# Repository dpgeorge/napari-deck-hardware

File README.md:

Napari Deck Hardware
====================

The Napari Deck is a custom keyboard-like USB HID input device with keys,
sliders, encoders and trackpads.  It is optimised for controlling [napari],
a multi-dimensional image viewer.

This repository contains the hardware design files needed to build a Napari
Deck: parts lists, 3D printed housing files and PCB design files.

Deck v1
-------

Napari Deck v1 is the first iteration of the housing and inputs (encoders, sliders,
buttons).  It is used to evaluate the inputs and the general layout of the deck.

It has the following inputs:
- mini trackball at the thumb position
- two keyboard switches
- two encoders
- iPod-like dial with encoder and five buttons
- mini joystick
- a slider (linear potentiometer)

Deck v2
-------

Napari Deck v2 is the second iteration of the housing and inputs, and is a fully
functional USB HID device that works with napari using `napari-deck-plugin`.

It has the following inputs:
- mini joystick at the thumb position for 3D rotation
- mini trackball at the thumb position for panning
- two encoders at the thumb position for rotation and zoom
- 16 keyboard switches
- three encoders for 3-axis slicing
- two sliders for opacity and brush size
- two sliders combined with a selection switch for four clipping planes

Deck mini
---------

Napari Deck Mini is a small device used to evaluate a mini trackpad and an encoder.
It is fully functional and works with napari.

It has the following inputs:
- mini trackpad
- encoder

Deck v3
-------

Napari Deck v3 is the third iteration of the housing and inputs.  It has a custom
PCB to simplify the construction, with a built-in STM32G0B1 microcontroller.

It has the following inputs:
- two mini trackpads at the thumb position for 2D panning and 3D rotation
- two encoders at the thumb position for zoom and 3D rotation
- 16 keyboard switches
- three encoders for 3-axis slicing
- two sliders for opacity and brush size
- two sliders combined with a 4-way selection switch for eight clipping planes

Deck v3 is currently a work-in-progress.

[napari]: https://github.com/napari/napari

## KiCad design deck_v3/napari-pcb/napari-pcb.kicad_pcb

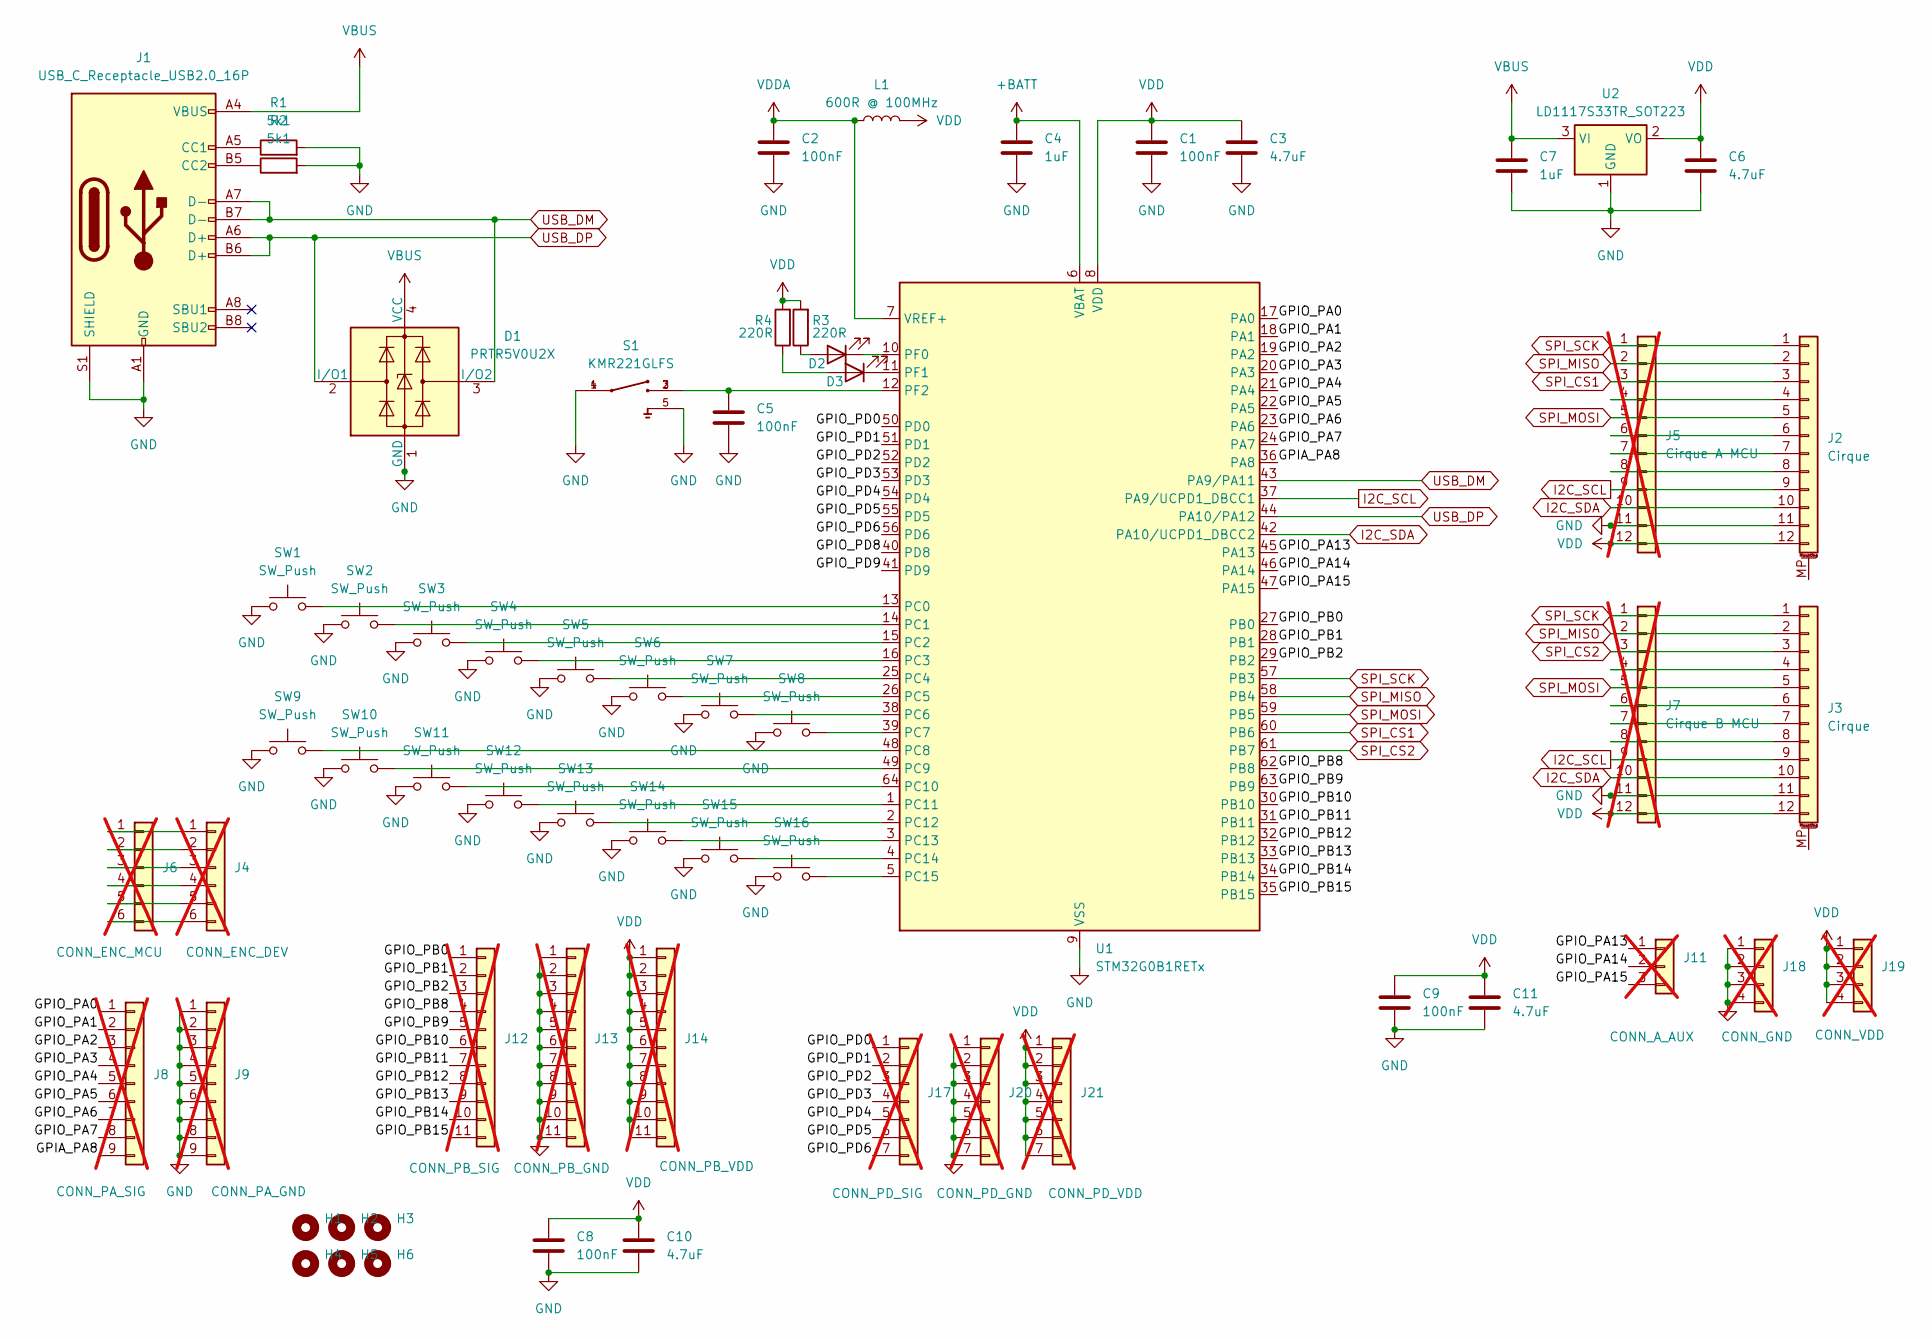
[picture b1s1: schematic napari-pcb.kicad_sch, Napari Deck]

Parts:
C1, C2, C5, C8, C9: 100nF; C_0603_1608Metric; LCSC Part # C14663
C3, C6, C10, C11: 4.7uF; C_0805_2012Metric; LCSC Part # C1779
C4, C7: 1uF; C_0603_1608Metric; LCSC Part # C15849
D1: PRTR5V0U2X; SOT-143; LCSC Part # C2827688
D2: LED; LED_0805_2012Metric; LCSC Part # C84256
D3: LED; LED_0805_2012Metric; LCSC Part # C2297
H1, H2, H3, H4, H5, H6: MountingHole; MountingHole_3.2mm_M3
J1: USB_C_Receptacle_USB2.0_16P; USB_C_Receptacle_Palconn_UTC16-G; LCSC Part # C165948
J2, J3: Cirque; Hirose_FH12-12S-0.5SH_1x12-1MP_P0.50mm_Horizontal; LCSC Part # C88360
J4: CONN_ENC_DEV; PinHeader_1x06_P1.27mm_Vertical; not fitted
J5: Cirque A MCU; PinHeader_1x12_P1.00mm_Vertical; not fitted
J6: CONN_ENC_MCU; PinHeader_1x06_P2.00mm_Vertical; not fitted
J7: Cirque B MCU; PinHeader_1x12_P1.00mm_Vertical; not fitted
J8: CONN_PA_SIG; PinHeader_1x09_P2.54mm_Vertical; not fitted
J9: CONN_PA_GND; PinHeader_1x09_P2.54mm_Vertical; not fitted
J11: CONN_A_AUX; PinHeader_1x03_P2.54mm_Vertical; not fitted
J12: CONN_PB_SIG; PinHeader_1x11_P2.54mm_Vertical; not fitted
J13: CONN_PB_GND; PinHeader_1x11_P2.54mm_Vertical; not fitted
J14: CONN_PB_VDD; PinHeader_1x11_P2.54mm_Vertical; not fitted
J17: CONN_PD_SIG; PinHeader_1x07_P2.54mm_Vertical; not fitted
J18: CONN_GND; PinHeader_1x04_P2.54mm_Vertical; not fitted
J19: CONN_VDD; PinHeader_1x04_P2.54mm_Vertical; not fitted
J20: CONN_PD_GND; PinHeader_1x07_P2.54mm_Vertical; not fitted
J21: CONN_PD_VDD; PinHeader_1x07_P2.54mm_Vertical; not fitted
L1: 600R @ 100MHz; L_0603_1608Metric; LCSC Part # C1002
R1, R2: 5k1; R_0603_1608Metric; LCSC Part # C23186
R3, R4: 220R; R_0603_1608Metric; LCSC Part # C22962
S1: KMR221GLFS; SW_KMR221GLFS; LCSC Part # C72443
SW1, SW2, SW3, SW4, SW5, SW6, SW7, SW8, SW9, SW10, SW11, SW12, SW13, SW14, SW15, SW16: SW_Push; keyswitch_cherrymx_hotswap_1u; LCSC Part # C41430893
U1: STM32G0B1RETx; LQFP-64_10x10mm_P0.5mm; LCSC Part # C2829307
U2: LD1117S33TR_SOT223; SOT-223-3_TabPin2; LCSC Part # C435835

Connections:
+BATT: C4.1, U1.6 (VBAT)
/GPIA_PA8: J8.9, U1.36 (PA8)
/GPIO_PA0: J8.1, U1.17 (PA0)
/GPIO_PA1: J8.2, U1.18 (PA1)
/GPIO_PA2: J8.3, U1.19 (PA2)
/GPIO_PA3: J8.4, U1.20 (PA3)
/GPIO_PA4: J8.5, U1.21 (PA4)
/GPIO_PA5: J8.6, U1.22 (PA5)
/GPIO_PA6: J8.7, U1.23 (PA6)
/GPIO_PA7: J8.8, U1.24 (PA7)
/GPIO_PA13: J11.1, U1.45 (PA13)
/GPIO_PA14: J11.2, U1.46 (PA14)
/GPIO_PA15: J11.3, U1.47 (PA15)
/GPIO_PB0: J12.1, U1.27 (PB0)
/GPIO_PB1: J12.2, U1.28 (PB1)
/GPIO_PB2: J12.3, U1.29 (PB2)
/GPIO_PB8: J12.4, U1.62 (PB8)
/GPIO_PB9: J12.5, U1.63 (PB9)
/GPIO_PB10: J12.6, U1.30 (PB10)
/GPIO_PB11: J12.7, U1.31 (PB11)
/GPIO_PB12: J12.8, U1.32 (PB12)
/GPIO_PB13: J12.9, U1.33 (PB13)
/GPIO_PB14: J12.10, U1.34 (PB14)
/GPIO_PB15: J12.11, U1.35 (PB15)
/GPIO_PD0: J17.1, U1.50 (PD0)
/GPIO_PD1: J17.2, U1.51 (PD1)
/GPIO_PD2: J17.3, U1.52 (PD2)
/GPIO_PD3: J17.4, U1.53 (PD3)
/GPIO_PD4: J17.5, U1.54 (PD4)
/GPIO_PD5: J17.6, U1.55 (PD5)
/GPIO_PD6: J17.7, U1.56 (PD6)
/GPIO_PD8: U1.40 (PD8)
/GPIO_PD9: U1.41 (PD9)
GND: C1.2, C2.2, C3.2, C4.2, C5.2, C6.2, C7.2, C8.2, C9.2, C10.2, C11.2, D1.1 (GND), J1.A1 (GND), J1.A12 (GND), J1.B1 (GND), J1.B12 (GND), J1.S1 (SHIELD), J2.11, J3.11, J5.11, J7.11, J9.1, J9.2, J9.3, J9.4, J9.5, J9.6, J9.7, J9.8, J9.9, J13.1, J13.2, J13.3, J13.4, J13.5, J13.6, J13.7, J13.8, J13.9, J13.10, J13.11, J18.1, J18.2, J18.3, J18.4, J20.1, J20.2, J20.3, J20.4, J20.5, J20.6, J20.7, R1.2, R2.2, S1.1, S1.4, S1.5, SW1.1, SW2.1, SW3.1, SW4.1, SW5.1, SW6.1, SW7.1, SW8.1, SW9.1, SW10.1, SW11.1, SW12.1, SW13.1, SW14.1, SW15.1, SW16.1, U1.9 (VSS), U2.1 (GND)
I2C_SCL: J2.9, J3.9, J5.9, J7.9, U1.37 (PA9/UCPD1_DBCC1)
I2C_SDA: J2.10, J3.10, J5.10, J7.10, U1.42 (PA10/UCPD1_DBCC2)
unnamed: D2.2 (A), R3.1
unnamed: D2.1 (K), U1.10 (PF0)
unnamed: D3.2 (A), R4.1
unnamed: D3.1 (K), U1.11 (PF1)
unnamed: J1.A5 (CC1), R1.1
unnamed: J1.B5 (CC2), R2.1
unnamed: J2.4, J5.4
unnamed: J2.6, J5.6
unnamed: J2.7, J5.7
unnamed: J2.8, J5.8
unnamed: J3.4, J7.4
unnamed: J3.6, J7.6
unnamed: J3.7, J7.7
unnamed: J3.8, J7.8
unnamed: J4.1, J6.1
unnamed: J4.2, J6.2
unnamed: J4.3, J6.3
unnamed: J4.4, J6.4
unnamed: J4.5, J6.5
unnamed: J4.6, J6.6
unnamed: SW1.2, U1.13 (PC0)
unnamed: SW2.2, U1.14 (PC1)
unnamed: SW3.2, U1.15 (PC2)
unnamed: SW4.2, U1.16 (PC3)
unnamed: SW5.2, U1.25 (PC4)
unnamed: SW6.2, U1.26 (PC5)
unnamed: SW7.2, U1.38 (PC6)
unnamed: SW8.2, U1.39 (PC7)
unnamed: SW9.2, U1.48 (PC8)
unnamed: SW10.2, U1.49 (PC9)
unnamed: SW11.2, U1.64 (PC10)
unnamed: SW12.2, U1.1 (PC11)
unnamed: SW13.2, U1.2 (PC12)
unnamed: SW14.2, U1.3 (PC13)
unnamed: SW15.2, U1.4 (PC14)
unnamed: SW16.2, U1.5 (PC15)
unnamed: C5.1, S1.2, S1.3, U1.12 (PF2)
SPI_CS1: J2.3, J5.3, U1.60 (PB6)
SPI_CS2: J3.3, J7.3, U1.61 (PB7)
SPI_MISO: J2.2, J3.2, J5.2, J7.2, U1.58 (PB4)
SPI_MOSI: J2.5, J3.5, J5.5, J7.5, U1.59 (PB5)
SPI_SCK: J2.1, J3.1, J5.1, J7.1, U1.57 (PB3)
USB_DM: D1.3 (I/O2), J1.A7 (D-), J1.B7 (D-), U1.43 (PA9/PA11)
USB_DP: D1.2 (I/O1), J1.A6 (D+), J1.B6 (D+), U1.44 (PA10/PA12)
VBUS: C7.1, D1.4 (VCC), J1.A4 (VBUS), J1.A9 (VBUS), J1.B4 (VBUS), J1.B9 (VBUS), U2.3 (VI)
VDD: C1.1, C3.1, C6.1, C8.1, C9.1, C10.1, C11.1, J2.12, J3.12, J5.12, J7.12, J14.1, J14.2, J14.3, J14.4, J14.5, J14.6, J14.7, J14.8, J14.9, J14.10, J14.11, J19.1, J19.2, J19.3, J19.4, J21.1, J21.2, J21.3, J21.4, J21.5, J21.6, J21.7, L1.2, R3.2, R4.2, U1.8 (VDD), U2.2 (VO)
VDDA: C2.1, L1.1, U1.7 (VREF+)

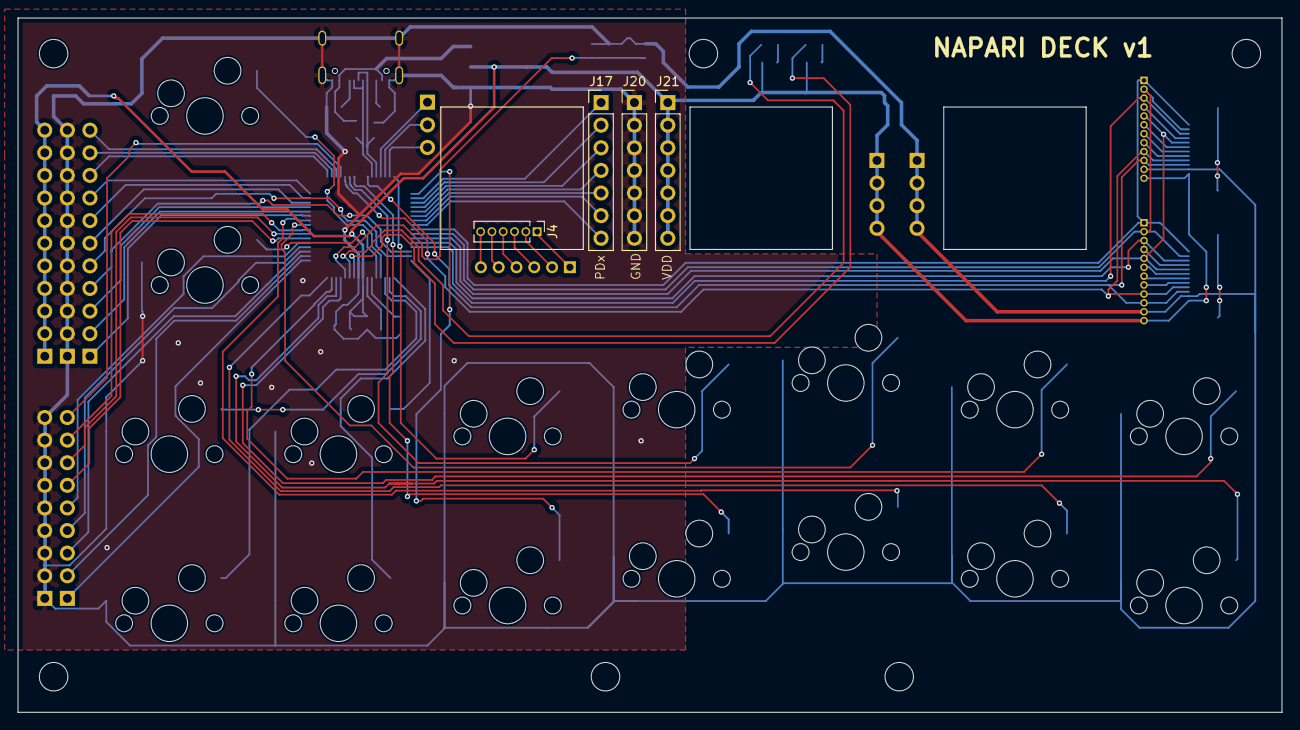
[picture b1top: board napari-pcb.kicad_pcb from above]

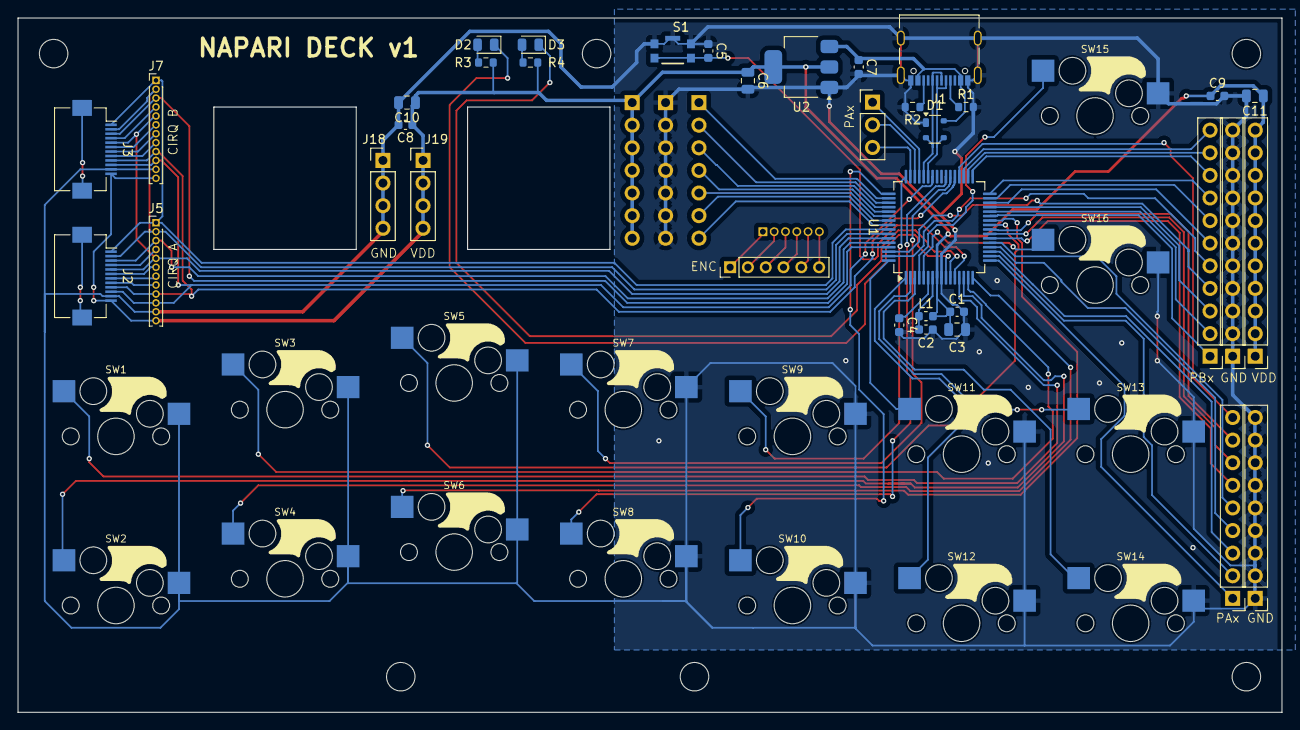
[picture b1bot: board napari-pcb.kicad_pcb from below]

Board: 2 copper layers, 142.0 x 78.0 mm, 62 parts (52 on the bottom side), 81 nets.

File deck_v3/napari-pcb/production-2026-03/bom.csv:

Designator,Footprint,Quantity,Value,LCSC Part #
"C1, C2, C5, C8, C9",0603,5,100nF,C14663
"C10, C11, C3, C6",0805,4,4.7uF,C1779
"C4, C7",0603,2,1uF,C15849
D1,SOT-143,1,PRTR5V0U2X,C2827688
D2,0805,1,LED,C84256
D3,0805,1,LED,C2297
J1,USB_C_Receptacle_Palconn_UTC16-G,1,USB_C_Receptacle_USB2.0_16P,C165948
"J2, J3",Hirose_FH12-12S-0.5SH_1x12-1MP_P0.50mm_Horizontal,2,Cirque,C88360
L1,0603,1,600R @ 100MHz,C1002
"R1, R2",0603,2,5k1,C23186
"R3, R4",0603,2,220R,C22962
S1,SW_KMR221GLFS,1,KMR221GLFS,C72443
"SW1, SW10, SW11, SW12, SW13, SW14, SW15, SW16, SW2, SW3, SW4, SW5, SW6, SW7, SW8, SW9",keyswitch_cherrymx_hotswap_1u,16,SW_Push,C41430893
U1,LQFP-64_10x10mm_P0.5mm,1,STM32G0B1RETx,C2829307
U2,SOT-223-3_TabPin2,1,LD1117S33TR_SOT223,C435835

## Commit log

2026-04-01 Initial commit.
    With a simple README.
2026-04-01 deck_v1: Add design and output files for napari deck v1.
2026-04-01 deck_v2: Add design and output files for napari deck v2.
2026-04-01 deck_mini: Add design and output files for napari mini deck.
2026-04-01 keycaps: Add design and output files for slider keycaps.
2026-04-01 keycaps: Add output file for pgup/pgdn keycaps.
    Generated using https://github.com/rsheldiii/KeyV2.
2026-04-01 deck_v3: Add PCB design files for deck v3.
2026-04-01 deck_v3: Add JLCPCB production files.
2026-04-02 deck_v3: Tweak schematic layout for improved visibility of components.
    No electrical change.
2026-04-02 deck_v3: Add schematic PDF and image of track layout for production run.
    And rename JLCPCB model image file to be consistent with the new files.
2026-04-02 README: Update README with description of the four decks.
